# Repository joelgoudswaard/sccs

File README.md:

<h1>
  
  The Singularity Camper Control System
</h1>

The SCCS is a control system for the electrics in your caravan or camper trailer. It replaces a switch panel and battery/water gauges etc. with a modern touchscreen UI that provides:
- Automated control of lighting based on sunset/sunrise times and door/panel open and closes.
- Display of important information:
  - Battery level and usage
  - Solar generation
  - Water tank levels
  - Location data
  - outside/fridge temperature and weather forecasts
  - Sonos speakers

The system is made up of a Raspberry Pi and custom PCB, the SCCS Core that is the central hub where all field wiring connects to.

The SCCS software configures the Raspberry Pi as a router so that Internet can be distributed from a USB/Wi-Fi hotspot or Starlink through a downstream WAP, enabling a local Wi-Fi network that gives your devices access to the UI and provides ad-filtered Internet access.

Networking services — NAT, DNS, DHCP, and ad-filtering — are provided by nftables and Pi-hole and configured during installation. That same LAN step installs UniFi OS Server so UniFi access points can be adopted locally at `https://10.10.10.1:11443`. Apple HomeKit and Google Home can be configured to enable voice commands of lighting through Siri or Gemini. Cloudflare Tunnels is supported for remote access to the system while away from the caravan/camper.

An interactive demo is available at [demo.singularityautomation.com.au](https://demo.singularityautomation.com.au).

## Getting started

## Quickstart

1. Order SCCS Core PCB from JLCPCB by uploading the contents of the `/kicad/production` folder to JLCPCB. Get PCBA (assembly) done as well - you will receive a warning during the component placement stage that the same component is mapped to multiple parts. This is intentional, tick the checkboxes to include them in the build and continue.
2. Install wiring and SCCS core.
3. Install the software with the install command:

```bash
curl -fsSL https://raw.githubusercontent.com/joelgoudswaard/sccs/main/install.sh -o /tmp/sccs-install.sh && sudo bash /tmp/sccs-install.sh
```

Full instructions are in the [project wiki](https://github.com/joelgoudswaard/sccs/wiki/).

## System overview

A touchscreen in the kitchen or similar area shows the main user interface and is also reachable from phones or tablets on the LAN:

- Dimmable lighting sliders with red/white anti-bug mode and on/off buttons for non-dimmable loads (water, lighting, fridge circuits)
- Ambient lights that fade on as it gets dark
- One-touch lighting scenes
- Control of Sonos speakers
- Light/dark UI themes and an extensive settings page
- Integration with Apple HomeKit and Google Home

## Display of Environmental information

- Water tank level
- Current temperature and fridge/freezer temperatures
- Current battery charge, voltage, current consumption, estimated power remaining and current/daily solar generation
- GPS coordinates, closest suburb, altitude, satellite quality, sunrise/sunset, and the day/evening/night timing that drives automation
- 4 Day weather forecast, humidity and expected overnight temperature if Internet is present
- Internet connection quality details
- What lights are on and what doors or panels are open
- Health status of connected hardware modules like solar or GPS

## Hardware architecture

- Raspberry Pi 4/5
- Dual ESP32-S3s for 16 channels of PWM dimming via MOSFETs
- u-blox NEO-M9N GPS for location data
- Victron SmartShunt and SmartSolar support for battery and solar monitoring
- WS281X addressable LED strip outputs
- 10A relays for non-dimmable loads like lighting circuits, floodlights and water pumps
- Reed switch inputs for door/panel sensing and triggering of lights
- 1-Wire bus for temperature sensors
- Water tank level sensor input
- Spare channels for everything for expansion

## Hardware and User Interface

### SCCS Core

<table>
  <tr>
    <td align="center" width="50%"></td>
    <td align="center" width="50%"></td>
  </tr>
  <tr>
    <td align="center"><strong>Top (bare board)</strong></td>
    <td align="center"><strong>Top (with Raspberry Pi fitted)</strong></td>
  </tr>
  <tr>
    <td align="center"></td>
    <td align="center"></td>
  </tr>
  <tr>
    <td align="center"><strong>Bottom</strong></td>
    <td align="center"><strong>Isometric (with Raspberry Pi fitted)</strong></td>
  </tr>
</table>

### 3D Printable Mount

<table>
  <tr>
    <td align="center" width="50%"></td>
    <td align="center" width="50%"></td>
  </tr>
  <tr>
    <td align="center"><strong>3D printable frame (top)</strong></td>
    <td align="center"><strong>3D printable frame (isometric)</strong></td>
  </tr>
</table>

### User Interface

<table>
  <tr>
    <td align="center" width="50%"></td>
    <td align="center" width="50%"></td>
  </tr>
  <tr>
    <td align="center"><strong>Neumorphism (Dark) — iPad</strong></td>
    <td align="center"><strong>Neumorphism (Light) — iPad</strong></td>
  </tr>
  <tr>
    <td align="center"></td>
    <td align="center"></td>
  </tr>
  <tr>
    <td align="center"><strong>Glassmorphism (Dark) — iPad</strong></td>
    <td align="center"><strong>Glassmorphism (Dark) — iPad Lighting</strong></td>
  </tr>
  <tr>
    <td align="center"></td>
    <td align="center"></td>
  </tr>
  <tr>
    <td align="center"><strong>Neumorphism (Dark) — iPhone Portrait</strong></td>
    <td align="center"><strong>Neumorphism (Dark) — iPhone Landscape</strong></td>
  </tr>
</table>

---

## Documentation

Wiring, installation, configuration, and optional packages are on the **[project wiki](https://github.com/joelgoudswaard/sccs/wiki)** (start at [Home](https://github.com/joelgoudswaard/sccs/wiki/Home) for the setup path and glossary).

| Topic | Wiki page |
|-------|-----------|
| Overview, setup path, glossary | [Home](https://github.com/joelgoudswaard/sccs/wiki/Home) |
| Shopping list and wiring | [Wiring and Hardware](https://github.com/joelgoudswaard/sccs/wiki/Wiring-and-Hardware) |
| Imaging the Pi and installer | [Software Installation](https://github.com/joelgoudswaard/sccs/wiki/Software-Installation) |
| `sccs.conf`, phases, lights, sensors | [Software Configuration](https://github.com/joelgoudswaard/sccs/wiki/Software-Configuration) |
| SmartShunt / SmartSolar Bluetooth | [Victron Setup](https://github.com/joelgoudswaard/sccs/wiki/Victron-Setup) |
| Apple Home app / Siri (optional) | [HomeKit](https://github.com/joelgoudswaard/sccs/wiki/HomeKit) |
| Google Home / Gemini (optional) | [Google Home](https://github.com/joelgoudswaard/sccs/wiki/Google-Home) |
| LAN, NAT, Pi-hole, USB internet | [Networking](https://github.com/joelgoudswaard/sccs/wiki/Networking) |
| UniFi controller (optional) | [UniFi OS Server](https://github.com/joelgoudswaard/sccs/wiki/UniFi-OS-Server) |

---

## License

Licensed under the [MIT License](LICENSE).

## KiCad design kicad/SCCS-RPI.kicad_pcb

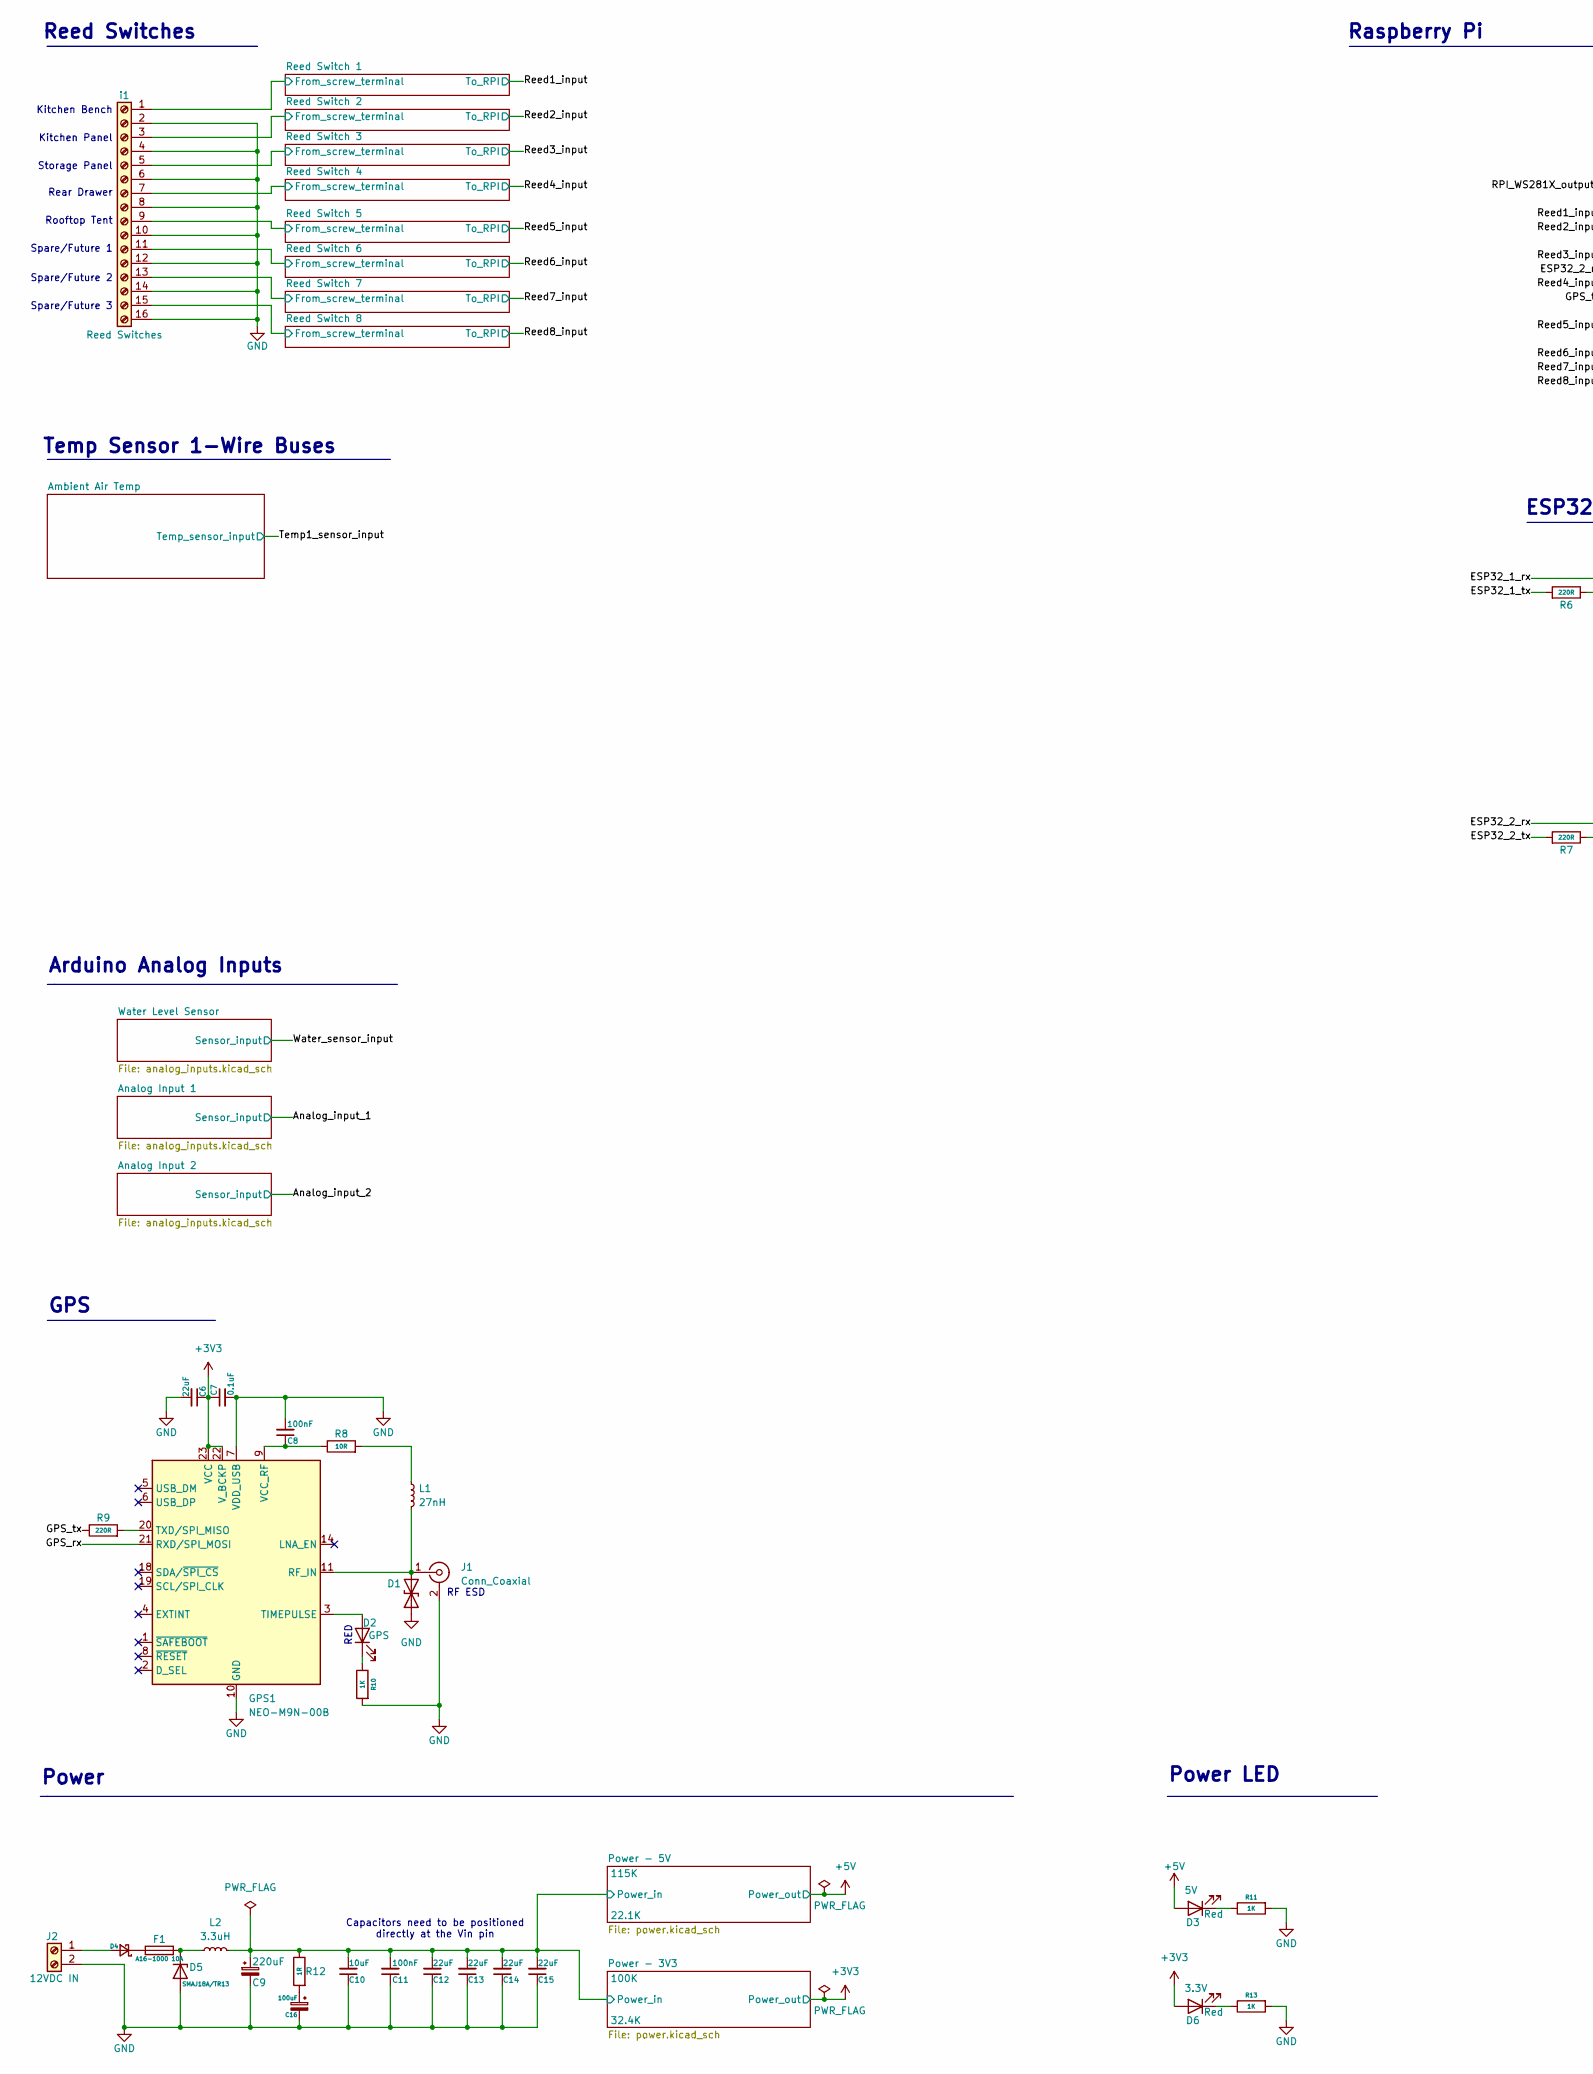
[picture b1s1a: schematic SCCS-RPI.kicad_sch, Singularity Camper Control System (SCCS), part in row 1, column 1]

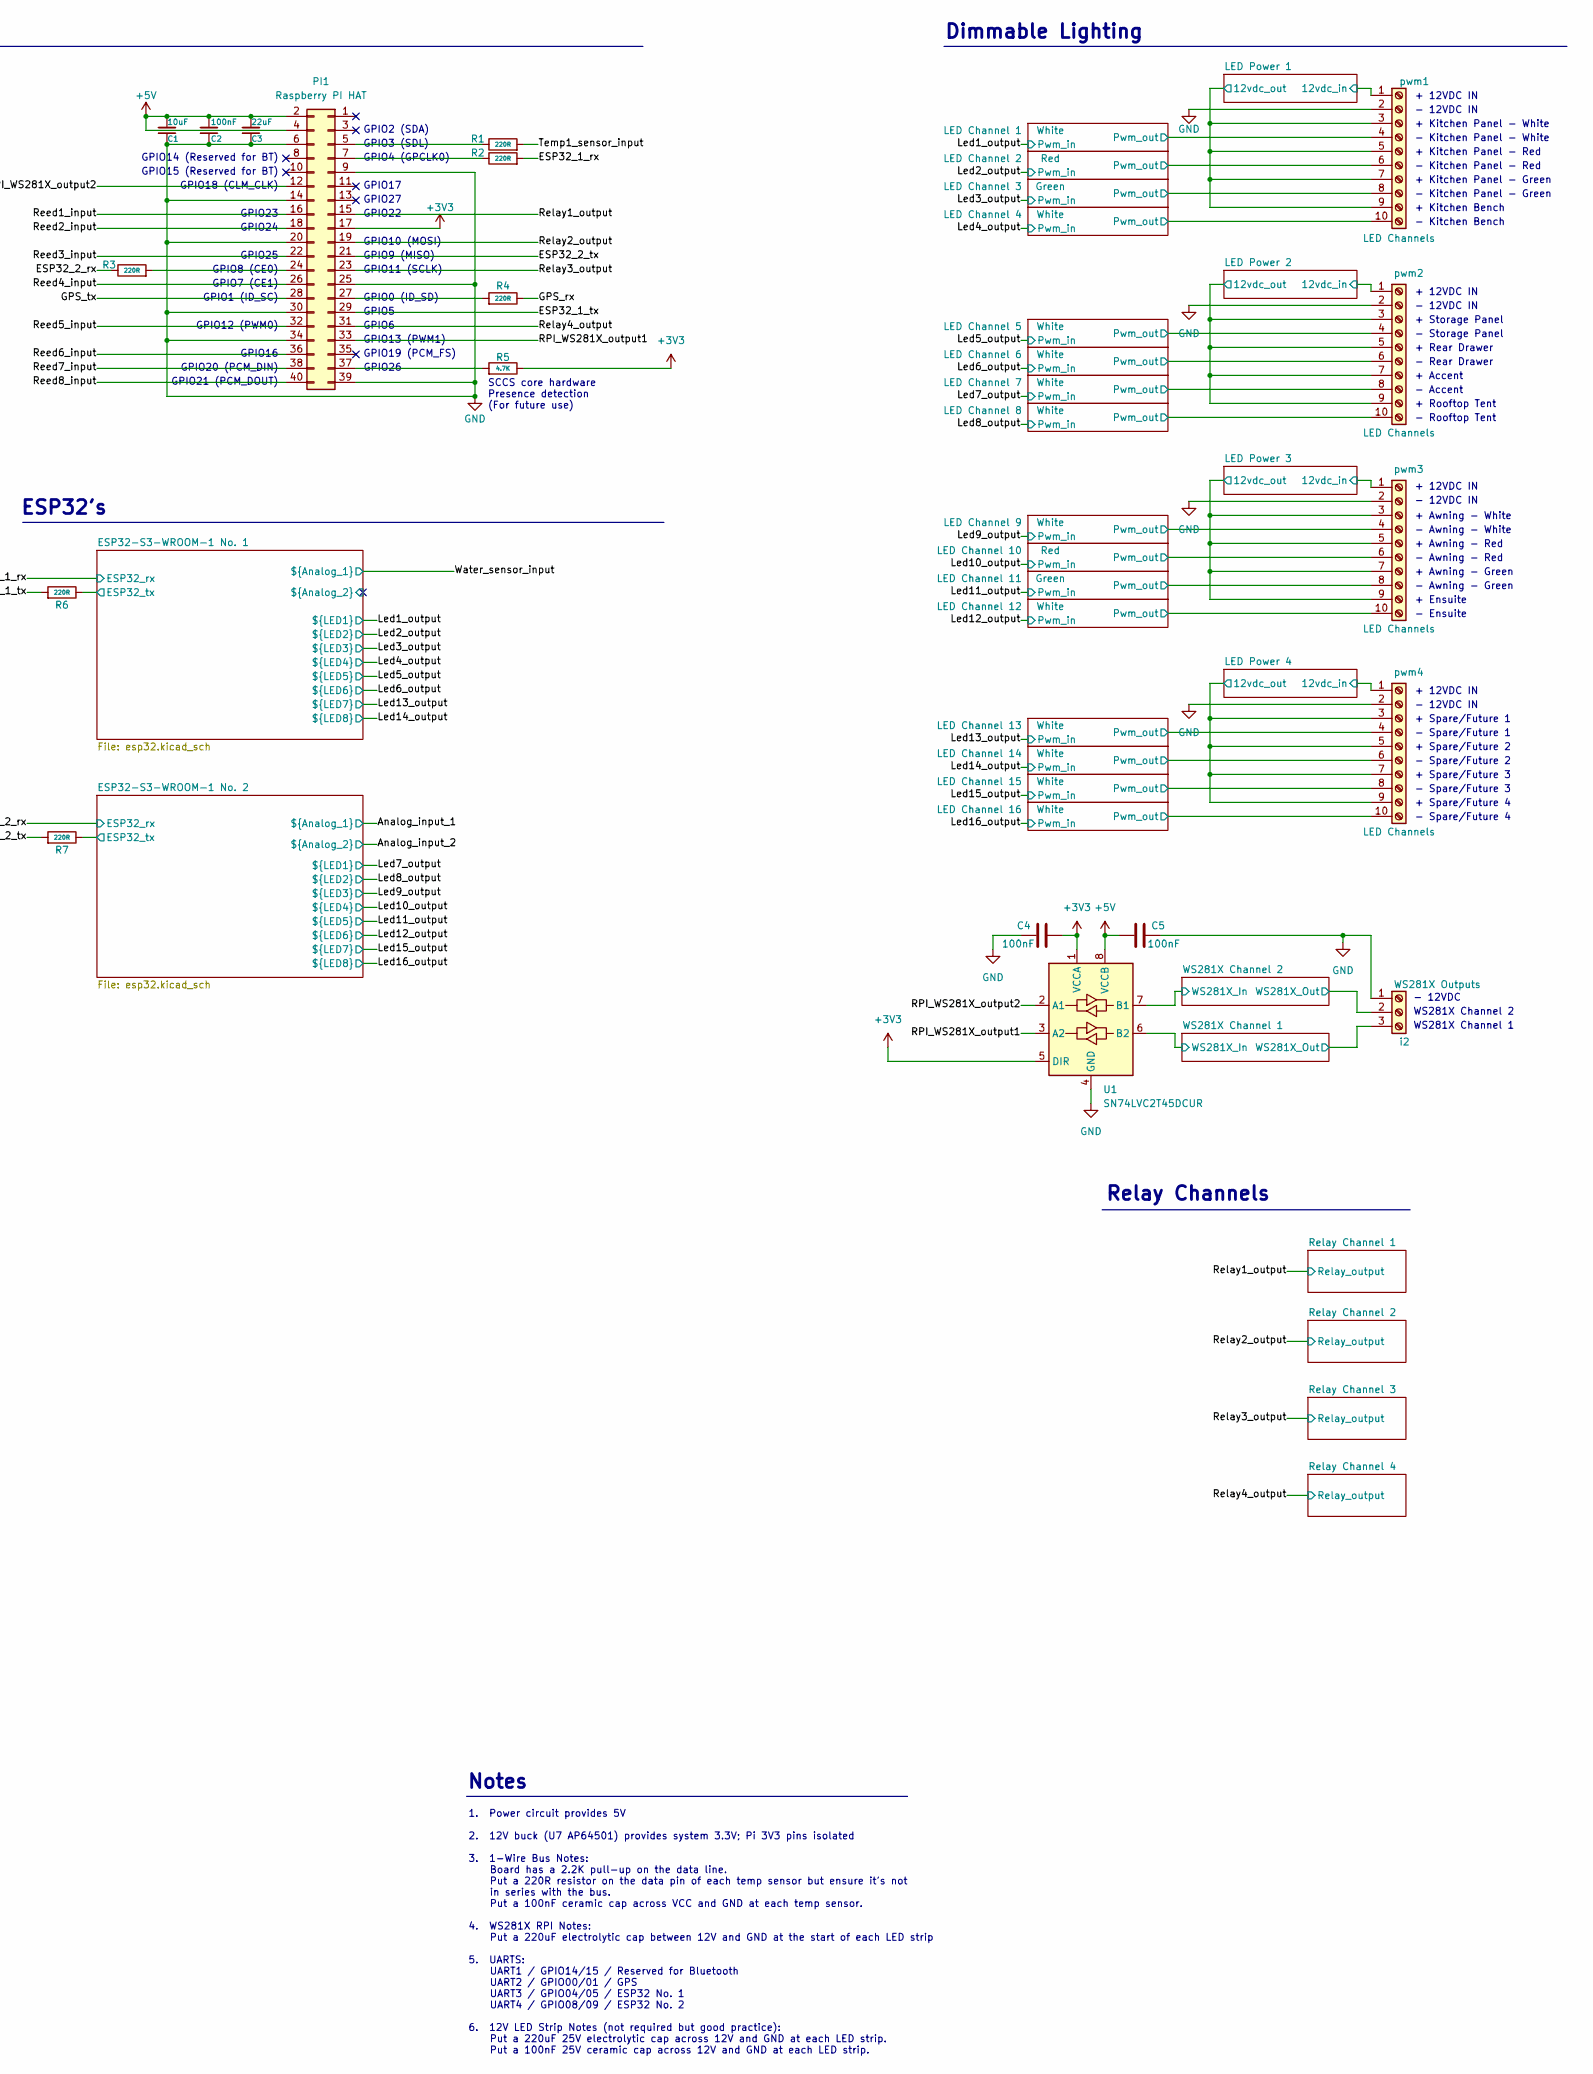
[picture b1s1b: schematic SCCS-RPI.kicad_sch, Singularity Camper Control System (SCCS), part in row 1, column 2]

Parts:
C1, C10: 10uF; C_0805_2012Metric; LCSC Part # C15850
C2, C8, C11: 100nF; C_0805_2012Metric; LCSC Part # C49678
C3, C6, C12, C13, C14, C15: 22uF; C_0805_2012Metric; LCSC Part # C86816
C4, C5: 100nF; C_0603_1608Metric; LCSC Part # C1590
C7: 0.1uF; C_0805_2012Metric; LCSC Part # C86041
C9: 220uF; CP_Elec_8x10; LCSC Part # C165536
C16: 100uF; CP_Radial_D6.3mm_P2.50mm; LCSC Part # C44587
D1: ESD103-B1-02EL; D_0402_1005Metric; LCSC Part # C535146
D2: GPS; LED_0603_1608Metric; LCSC Part # C2286
D3: 5V; LED_0603_1608Metric; LCSC Part # C2286
D4: D_PowerDI-5; LCSC Part # C2759901
D5: SMAJ18A/TR13; D_SMB; LCSC Part # C571369
D6: 3.3V; LED_0603_1608Metric; LCSC Part # C2286
F1: A16-1000 10A; Fuse_Bourns_MF-RG1000; LCSC Part # C135398
GPS1: NEO-M9N-00B; ublox_NEO; LCSC Part # C5119087
J1: Conn_Coaxial; SMA_Amphenol_132134-11_Vertical; LCSC Part # C20415804
J2: 12VDC IN; TerminalBlock_Phoenix_MKDS-1,5-2-5.08_1x02_P5.08mm_Horizont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; LCSC Part # C8445
L1: 27nH; L_0603_1608Metric; LCSC Part # C162550
L2: 3.3uH; L_SXN_SMDRI127; LCSC Part # C24550
PI1: Raspberry PI HAT; PinSocket_2x20_P2.54mm_Vertical; LCSC Part # C132132
R1, R2, R3, R4, R6, R7, R9: 220R; R_0805_2012Metric; LCSC Part # C17557
R5: 4.7K; R_0805_2012Metric; LCSC Part # C17673
R8: 10R; R_0805_2012Metric; LCSC Part # C17415
R10, R11, R13: 1K; R_0402_1005Metric; LCSC Part # C11702
R12: 1R; R_0805_2012Metric; LCSC Part # C25271
U1: SN74LVC2T45DCUR; VSSOP-8_2.3x2mm_P0.5mm; LCSC Part # C15741
i1: Reed Switches; TerminalBlock_Phoenix_MKDS-1,5-16-5.08_1x16_P5.08mm_Horizon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; LCSC Part # C508906
i2: WS281X Outputs; TerminalBlock_Phoenix_MKDS-1,5-3-5.08_1x03_P5.08mm_Horizont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; LCSC Part # C8412
pwm1, pwm2, pwm3, pwm4: LED Channels; TerminalBlock_Phoenix_MKDS-1,5-10-5.08_1x10_P5.08mm_Horizon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; LCSC Part # C29173

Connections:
+3V3: C4.2, C6.1, C7.1, D6.2 (A), GPS1.22 (V_BCKP), GPS1.23 (VCC), PI1.17, R5.1, U1.1 (VCCA), U1.5 (DIR); also elsewhere on the board
+5V: C1.2, C2.2, C3.2, C5.2, D3.2 (A), PI1.2, PI1.4, U1.8 (VCCB); also elsewhere on the board
/ESP32-S3-WROOM-1 No. 1/ESP32_tx: R6.1; also elsewhere on the board
/ESP32-S3-WROOM-1 No. 2/ESP32_tx: R7.1; also elsewhere on the board
/ESP32_1_rx: R2.2; also elsewhere on the board
/ESP32_1_tx: PI1.29, R6.2
/ESP32_2_rx: R3.1; also elsewhere on the board
/ESP32_2_tx: PI1.21, R7.2
/GPS_rx: GPS1.21 (RXD/SPI_MOSI), R4.1
/GPS_tx: PI1.28, R9.1
/LED Channel 1/Pwm_out: pwm1.4; also elsewhere on the board
/LED Channel 2/Pwm_out: pwm1.6; also elsewhere on the board
/LED Channel 3/Pwm_out: pwm1.8; also elsewhere on the board
/LED Channel 4/Pwm_out: pwm1.10; also elsewhere on the board
/LED Channel 5/Pwm_out: pwm2.4; also elsewhere on the board
/LED Channel 6/Pwm_out: pwm2.6; also elsewhere on the board
/LED Channel 7/Pwm_out: pwm2.8; also elsewhere on the board
/LED Channel 8/Pwm_out: pwm2.10; also elsewhere on the board
/LED Channel 9/Pwm_out: pwm3.4; also elsewhere on the board
/LED Channel 10/Pwm_out: pwm3.6; also elsewhere on the board
/LED Channel 11/Pwm_out: pwm3.8; also elsewhere on the board
/LED Channel 12/Pwm_out: pwm3.10; also elsewhere on the board
/LED Channel 13/Pwm_out: pwm4.4; also elsewhere on the board
/LED Channel 14/Pwm_out: pwm4.6; also elsewhere on the board
/LED Channel 15/Pwm_out: pwm4.8; also elsewhere on the board
/LED Channel 16/Pwm_out: pwm4.10; also elsewhere on the board
/LED Power 1/12vdc_in: pwm1.1; also elsewhere on the board
/LED Power 1/12vdc_out: pwm1.3, pwm1.5, pwm1.7, pwm1.9; also elsewhere on the board
/LED Power 2/12vdc_in: pwm2.1; also elsewhere on the board
/LED Power 2/12vdc_out: pwm2.3, pwm2.5, pwm2.7, pwm2.9; also elsewhere on the board
/LED Power 3/12vdc_in: pwm3.1; also elsewhere on the board
/LED Power 3/12vdc_out: pwm3.3, pwm3.5, pwm3.7, pwm3.9; also elsewhere on the board
/LED Power 4/12vdc_in: pwm4.1; also elsewhere on the board
/LED Power 4/12vdc_out: pwm4.3, pwm4.5, pwm4.7, pwm4.9; also elsewhere on the board
/Power - 3V3/Power_in: C9.1, C10.2, C11.2, C12.2, C13.2, C14.2, C15.2, L2.2, R12.1; also elsewhere on the board
/RPI_WS281X_output1: PI1.33, U1.3 (A2)
/RPI_WS281X_output2: PI1.12, U1.2 (A1)
/Reed1_input: PI1.16; also elsewhere on the board
/Reed2_input: PI1.18; also elsewhere on the board
/Reed3_input: PI1.22; also elsewhere on the board
/Reed4_input: PI1.26; also elsewhere on the board
/Reed5_input: PI1.32; also elsewhere on the board
/Reed6_input: PI1.36; also elsewhere on the board
/Reed7_input: PI1.38; also elsewhere on the board
/Reed8_input: PI1.40; also elsewhere on the board
/Reed Switch 1/From_screw_terminal: i1.1; also elsewhere on the board
/Reed Switch 2/From_screw_terminal: i1.3; also elsewhere on the board
/Reed Switch 3/From_screw_terminal: i1.5; also elsewhere on the board
/Reed Switch 4/From_screw_terminal: i1.7; also elsewhere on the board
/Reed Switch 5/From_screw_terminal: i1.9; also elsewhere on the board
/Reed Switch 6/From_screw_terminal: i1.11; also elsewhere on the board
/Reed Switch 7/From_screw_terminal: i1.13; also elsewhere on the board
/Reed Switch 8/From_screw_terminal: i1.15; also elsewhere on the board
/Relay1_output: PI1.15; also elsewhere on the board
/Relay2_output: PI1.19; also elsewhere on the board
/Relay3_output: PI1.23; also elsewhere on the board
/Relay4_output: PI1.31; also elsewhere on the board
/Temp1_sensor_input: R1.2; also elsewhere on the board
/WS281X Channel 1/WS281X_In: U1.6 (B2); also elsewhere on the board
/WS281X Channel 1/WS281X_Out: i2.3; also elsewhere on the board
/WS281X Channel 2/WS281X_In: U1.7 (B1); also elsewhere on the board
/WS281X Channel 2/WS281X_Out: i2.2; also elsewhere on the board
GND: C1.1, C2.1, C3.1, C4.1, C5.1, C6.2, C7.2, C8.2, C9.2, C10.1, C11.1, C12.1, C13.1, C14.1, C15.1, C16.2, D1.1 (A1), D5.2 (A), GPS1.7 (VDD_USB), GPS1.10 (GND), GPS1.12 (GND), GPS1.13 (GND), GPS1.24 (GND), J1.2 (Ext), J2.2, PI1.6, PI1.9, PI1.14, PI1.20, PI1.25, PI1.30, PI1.34, PI1.39, R10.2, R11.2, R13.2, U1.4 (GND), i1.2, i1.4, i1.6, i1.8, i1.10, i1.12, i1.14, i1.16, i2.1, pwm1.2, pwm2.2, pwm3.2, pwm4.2; also elsewhere on the board
unnamed: C16.1, R12.2
unnamed: D1.2 (A2), GPS1.11 (RF_IN), J1.1 (In), L1.2
unnamed: D2.2 (A), GPS1.3 (TIMEPULSE)
unnamed: D2.1 (K), R10.1
unnamed: D3.1 (K), R11.1
unnamed: D4.2 (A), J2.1
unnamed: D4.1 (K), F1.1
unnamed: D5.1 (K), F1.2, L2.1
unnamed: D6.1 (K), R13.1
unnamed: GPS1.20 (TXD/SPI_MISO), R9.2
unnamed: C8.1, GPS1.9 (VCC_RF), R8.1
unnamed: L1.1, R8.2
unnamed: PI1.5, R1.1
unnamed: PI1.7, R2.1
unnamed: PI1.24, R3.2
unnamed: PI1.27, R4.2
unnamed: PI1.37, R5.2

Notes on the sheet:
+ Awning - White
- Spare/Future 3
GPIO1 (ID_SC)
Capacitors need to be positioned directly at the Vin pin
+ Spare/Future 1
WS281X Channel 1
GPIO12 (PWM0)
Rooftop Tent
Temp Sensor 1-Wire Buses
GPIO15 (Reserved for BT)
- 12VDC IN
SCCS core hardware Presence detection (For future use)
GPIO22
GPIO23
- Kitchen Panel - Red
Spare/Future 3
GPIO20 (PCM_DIN)
1. Power circuit provides 5V 2. 12V buck (U7 AP64501) provides system 3.3V; Pi 3V3 pins isolated 3. 1-Wire Bus Notes: Board has a 2.2K pull-up on the data line. Put a 220R resistor on the data pin of each temp sensor but ensure it's not in series with the bus. Put a 100nF ceramic cap across VCC and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
- Rear Drawer
ESP32's
+ Kitchen Bench
- Accent
RF ESD
GPIO25
GPIO27
+ 12VDC IN
GPIO11 (SCLK)
+ Storage Panel
+ Ensuite
- Kitchen Bench
GPIO7 (CE1)
Kitchen Bench
Notes
- Spare/Future 1
GPS
GPIO4 (GPCLK0)
- Rooftop Tent
Spare/Future 2
GPIO3 (SDL)
+ Awning - Green

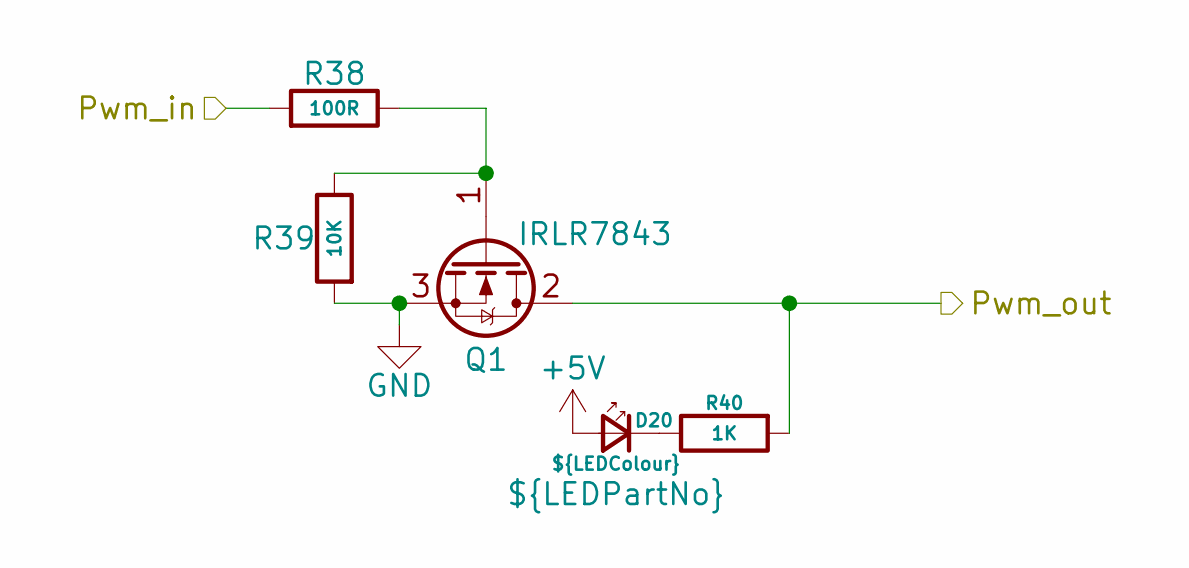
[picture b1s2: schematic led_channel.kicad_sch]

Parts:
D20: ${LEDColour}; LED_0603_1608Metric; LCSC Part # ${LEDPartNo}
Q1: IRLR7843; TO-252-2; LCSC Part # C21988
R38: 100R; R_0805_2012Metric; LCSC Part # C17408
R39: 10K; R_0805_2012Metric; LCSC Part # C17414
R40: 1K; R_0805_2012Metric; LCSC Part # C17513

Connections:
+5V: D20.2 (A); also elsewhere on the board
/LED Channel 1/Pwm_out: Q1.2 (D), R40.2; also elsewhere on the board
/Led1_output: R38.2; also elsewhere on the board
GND: Q1.3 (S), R39.2; also elsewhere on the board
unnamed: D20.1 (K), R40.1
unnamed: Q1.1 (G), R38.1, R39.1

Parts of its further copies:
Q2, Q3, Q4, Q5, Q6, Q7, Q8, Q9, Q10, Q11, Q12, Q13, Q14, Q15, Q16: IRLR7843; TO-252-2; LCSC Part # C21988
R41, R44, R47, R50, R53, R56, R59, R62, R65, R68, R71, R74, R77, R80, R83: 100R; R_0805_2012Metric; LCSC Part # C17408
R42, R45, R48, R51, R54, R57, R60, R63, R66, R69, R72, R75, R78, R81, R84: 10K; R_0805_2012Metric; LCSC Part # C17414
R43, R46, R49, R52, R55, R58, R61, R64, R67, R70, R73, R76, R79, R82, R85: 1K; R_0805_2012Metric; LCSC Part # C17513

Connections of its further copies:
/LED Channel 2/Pwm_out: Q2.2 (D), R43.2; also elsewhere on the board
/LED Channel 3/Pwm_out: Q3.2 (D), R46.2; also elsewhere on the board
/LED Channel 4/Pwm_out: Q4.2 (D), R49.2; also elsewhere on the board
/LED Channel 5/Pwm_out: Q5.2 (D), R52.2; also elsewhere on the board
/LED Channel 6/Pwm_out: Q6.2 (D), R55.2; also elsewhere on the board
/LED Channel 7/Pwm_out: Q7.2 (D), R58.2; also elsewhere on the board
/LED Channel 8/Pwm_out: Q8.2 (D), R61.2; also elsewhere on the board
/LED Channel 9/Pwm_out: Q9.2 (D), R64.2; also elsewhere on the board
/LED Channel 10/Pwm_out: Q10.2 (D), R67.2; also elsewhere on the board
/LED Channel 11/Pwm_out: Q11.2 (D), R70.2; also elsewhere on the board
/LED Channel 12/Pwm_out: Q12.2 (D), R73.2; also elsewhere on the board
/LED Channel 13/Pwm_out: Q13.2 (D), R76.2; also elsewhere on the board
/LED Channel 14/Pwm_out: Q14.2 (D), R79.2; also elsewhere on the board
/LED Channel 15/Pwm_out: Q15.2 (D), R82.2; also elsewhere on the board
/LED Channel 16/Pwm_out: Q16.2 (D), R85.2; also elsewhere on the board
/Led2_output: R41.2; also elsewhere on the board
/Led3_output: R44.2; also elsewhere on the board
/Led4_output: R47.2; also elsewhere on the board
/Led5_output: R50.2; also elsewhere on the board
/Led6_output: R53.2; also elsewhere on the board
/Led7_output: R56.2; also elsewhere on the board
/Led8_output: R59.2; also elsewhere on the board
/Led9_output: R62.2; also elsewhere on the board
/Led10_output: R65.2; also elsewhere on the board
/Led11_output: R68.2; also elsewhere on the board
/Led12_output: R71.2; also elsewhere on the board
/Led13_output: R74.2; also elsewhere on the board
/Led14_output: R77.2; also elsewhere on the board
/Led15_output: R80.2; also elsewhere on the board
/Led16_output: R83.2; also elsewhere on the board
GND: Q2.3 (S), Q3.3 (S), Q4.3 (S), Q5.3 (S), Q6.3 (S), Q7.3 (S), Q8.3 (S), Q9.3 (S), Q10.3 (S), Q11.3 (S), Q12.3 (S), Q13.3 (S), Q14.3 (S), Q15.3 (S), Q16.3 (S), R42.2, R45.2, R48.2, R51.2, R54.2, R57.2, R60.2, R63.2, R66.2, R69.2, R72.2, R75.2, R78.2, R81.2, R84.2; also elsewhere on the board
unnamed 95: R43.1; also elsewhere on the board
unnamed 96: R46.1; also elsewhere on the board
unnamed 97: R49.1; also elsewhere on the board
unnamed 98: R52.1; also elsewhere on the board
unnamed 99: R55.1; also elsewhere on the board
unnamed 100: R58.1; also elsewhere on the board
unnamed 101: R61.1; also elsewhere on the board
unnamed 102: R64.1; also elsewhere on the board
unnamed 103: R67.1; also elsewhere on the board
unnamed 104: R70.1; also elsewhere on the board
unnamed 105: R73.1; also elsewhere on the board
unnamed 106: R76.1; also elsewhere on the board
unnamed 107: R79.1; also elsewhere on the board
unnamed 108: R82.1; also elsewhere on the board
unnamed 109: R85.1; also elsewhere on the board
unnamed: Q2.1 (G), R41.1, R42.1
unnamed: Q3.1 (G), R44.1, R45.1
unnamed: Q4.1 (G), R47.1, R48.1
unnamed: Q5.1 (G), R50.1, R51.1
unnamed: Q6.1 (G), R53.1, R54.1
unnamed: Q7.1 (G), R56.1, R57.1
unnamed: Q8.1 (G), R59.1, R60.1
unnamed: Q9.1 (G), R62.1, R63.1
unnamed: Q10.1 (G), R65.1, R66.1
unnamed: Q11.1 (G), R68.1, R69.1
unnamed: Q12.1 (G), R71.1, R72.1
unnamed: Q13.1 (G), R74.1, R75.1
unnamed: Q14.1 (G), R77.1, R78.1
unnamed: Q15.1 (G), R80.1, R81.1
unnamed: Q16.1 (G), R83.1, R84.1

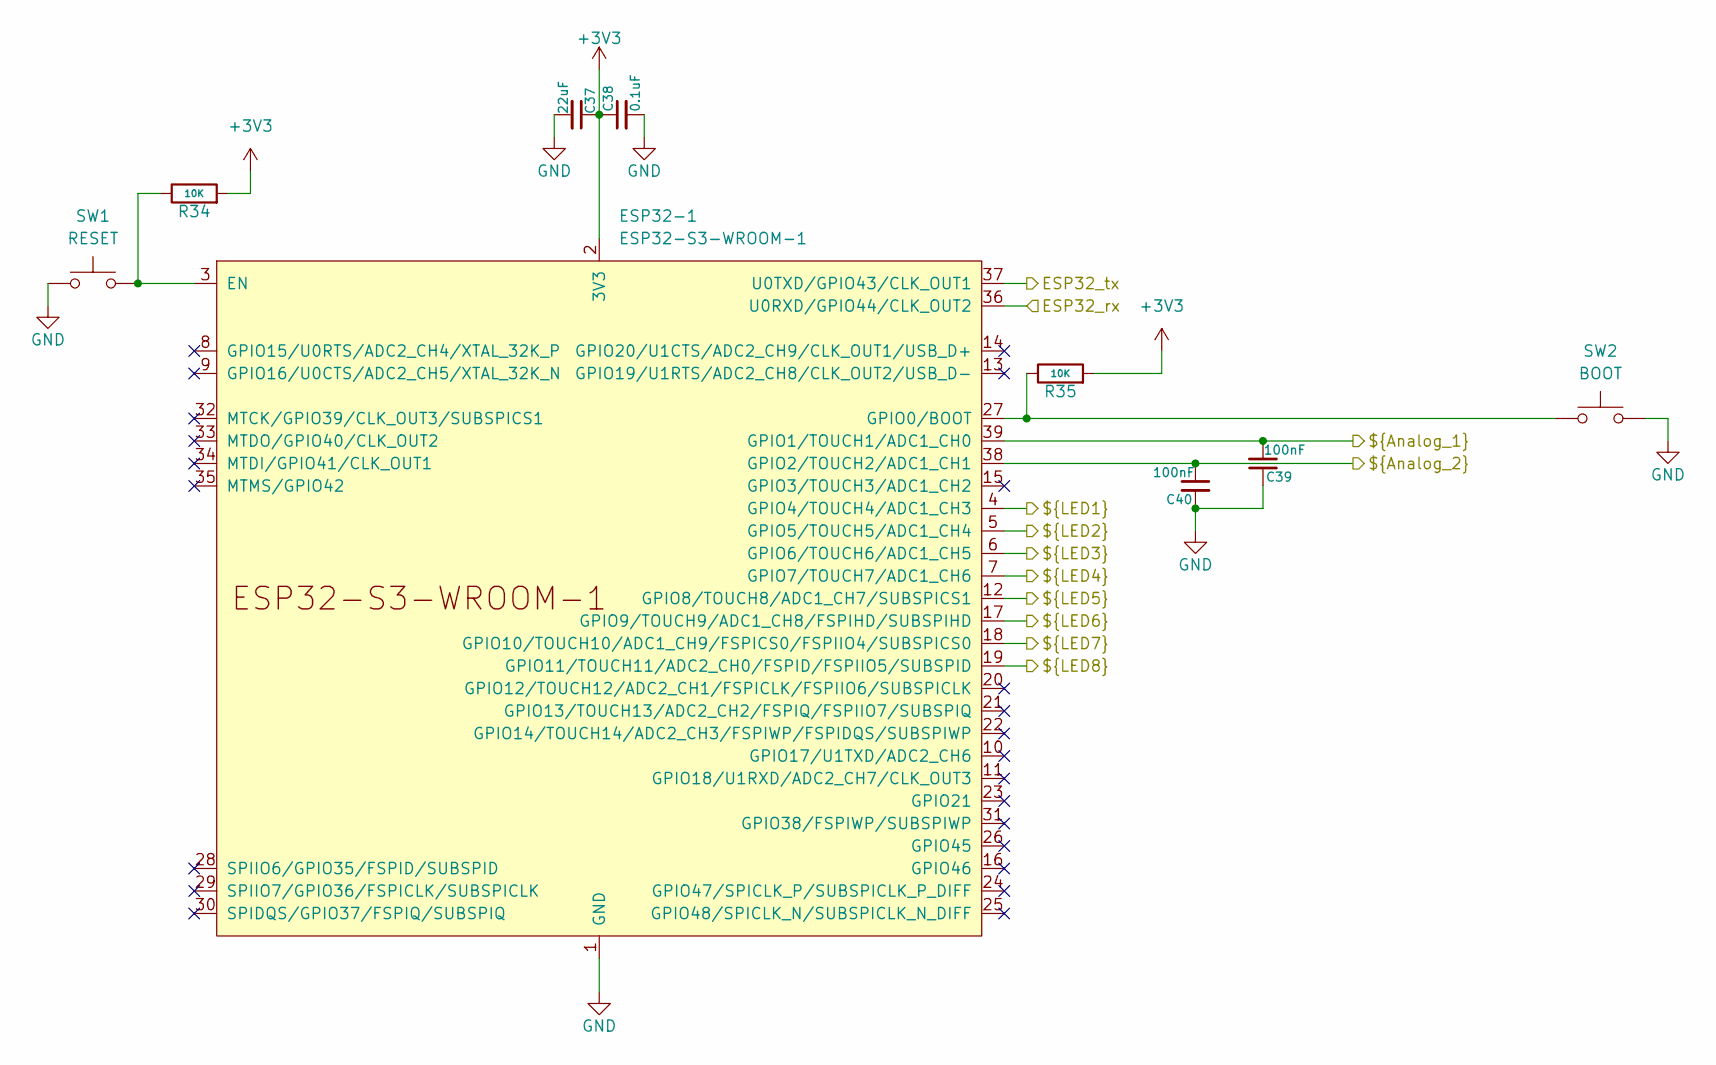
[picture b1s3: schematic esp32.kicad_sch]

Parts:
C37: 22uF; C_0805_2012Metric; LCSC Part # C86816
C38: 0.1uF; C_0805_2012Metric; LCSC Part # C86041
C39, C40: 100nF; C_0402_1005Metric; LCSC Part # C60474
ESP32-1: ESP32-S3-WROOM-1; ESP32-S3-WROOM-1U; LCSC Part # C3013946
R34, R35: 10K; R_0402_1005Metric; LCSC Part # C60490
SW1: RESET; SW_PUSH_1P1T_6x3.5mm_H5.0_APEM_MJTP1250; LCSC Part # C500070
SW2: BOOT; SW_PUSH_1P1T_6x3.5mm_H5.0_APEM_MJTP1250; LCSC Part # C500070

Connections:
+3V3: C37.1, C38.1, ESP32-1.2 (3V3), R34.2, R35.2; also elsewhere on the board
/ESP32-S3-WROOM-1 No. 1/ESP32_tx: ESP32-1.37 (U0TXD/GPIO43/CLK_OUT1); also elsewhere on the board
/ESP32-S3-WROOM-1 No. 1/NC: C40.1, ESP32-1.38 (GPIO2/TOUCH2/ADC1_CH1)
/ESP32_1_rx: ESP32-1.36 (U0RXD/GPIO44/CLK_OUT2); also elsewhere on the board
/Led1_output: ESP32-1.4 (GPIO4/TOUCH4/ADC1_CH3); also elsewhere on the board
/Led2_output: ESP32-1.5 (GPIO5/TOUCH5/ADC1_CH4); also elsewhere on the board
/Led3_output: ESP32-1.6 (GPIO6/TOUCH6/ADC1_CH5); also elsewhere on the board
/Led4_output: ESP32-1.7 (GPIO7/TOUCH7/ADC1_CH6); also elsewhere on the board
/Led5_output: ESP32-1.12 (GPIO8/TOUCH8/ADC1_CH7/SUBSPICS1); also elsewhere on the board
/Led6_output: ESP32-1.17 (GPIO9/TOUCH9/ADC1_CH8/FSPIHD/SUBSPIHD); also elsewhere on the board
/Led13_output: ESP32-1.18 (GPIO10/TOUCH10/ADC1_CH9/FSPICS0/FSPIIO4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); also elsewhere on the board
/Led14_output: ESP32-1.19 (GPIO11/TOUCH11/ADC2_CH0/FSPID/FSPIIO5/S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); also elsewhere on the board
/Water_sensor_input: C39.2, ESP32-1.39 (GPIO1/TOUCH1/ADC1_CH0); also elsewhere on the board
GND: C37.2, C38.2, C39.1, C40.2, ESP32-1.1 (GND), ESP32-1.40 (GND), ESP32-1.41 (GND), SW1.1, SW2.1; also elsewhere on the board
unnamed: ESP32-1.3 (EN), R34.1, SW1.2
unnamed: ESP32-1.27 (GPIO0/BOOT), R35.1, SW2.2

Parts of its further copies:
C41: 22uF; C_0805_2012Metric; LCSC Part # C86816
C42: 0.1uF; C_0805_2012Metric; LCSC Part # C86041
C43, C44: 100nF; C_0402_1005Metric; LCSC Part # C60474
ESP32-2: ESP32-S3-WROOM-1; ESP32-S3-WROOM-1U; LCSC Part # C3013946
R36, R37: 10K; R_0402_1005Metric; LCSC Part # C60490
SW3: RESET; SW_PUSH_1P1T_6x3.5mm_H5.0_APEM_MJTP1250; LCSC Part # C500070
SW4: BOOT; SW_PUSH_1P1T_6x3.5mm_H5.0_APEM_MJTP1250; LCSC Part # C500070

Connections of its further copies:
+3V3: C41.1, C42.1, ESP32-2.2 (3V3), R36.2, R37.2; also elsewhere on the board
/Analog_input_1: C43.2, ESP32-2.39 (GPIO1/TOUCH1/ADC1_CH0); also elsewhere on the board
/Analog_input_2: C44.1, ESP32-2.38 (GPIO2/TOUCH2/ADC1_CH1); also elsewhere on the board
/ESP32-S3-WROOM-1 No. 2/ESP32_tx: ESP32-2.37 (U0TXD/GPIO43/CLK_OUT1); also elsewhere on the board
/ESP32_2_rx: ESP32-2.36 (U0RXD/GPIO44/CLK_OUT2); also elsewhere on the board
/Led7_output: ESP32-2.4 (GPIO4/TOUCH4/ADC1_CH3); also elsewhere on the board
/Led8_output: ESP32-2.5 (GPIO5/TOUCH5/ADC1_CH4); also elsewhere on the board
/Led9_output: ESP32-2.6 (GPIO6/TOUCH6/ADC1_CH5); also elsewhere on the board
/Led10_output: ESP32-2.7 (GPIO7/TOUCH7/ADC1_CH6); also elsewhere on the board
/Led11_output: ESP32-2.12 (GPIO8/TOUCH8/ADC1_CH7/SUBSPICS1); also elsewhere on the board
/Led12_output: ESP32-2.17 (GPIO9/TOUCH9/ADC1_CH8/FSPIHD/SUBSPIHD); also elsewhere on the board
/Led15_output: ESP32-2.18 (GPIO10/TOUCH10/ADC1_CH9/FSPICS0/FSPIIO4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); also elsewhere on the board
/Led16_output: ESP32-2.19 (GPIO11/TOUCH11/ADC2_CH0/FSPID/FSPIIO5/S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); also elsewhere on the board
GND: C41.2, C42.2, C43.1, C44.2, ESP32-2.1 (GND), ESP32-2.40 (GND), ESP32-2.41 (GND), SW3.1, SW4.1; also elsewhere on the board
unnamed: ESP32-2.3 (EN), R36.1, SW3.2
unnamed: ESP32-2.27 (GPIO0/BOOT), R37.1, SW4.2

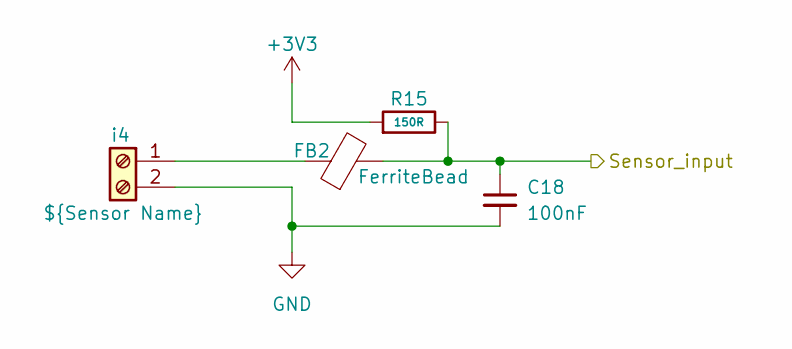
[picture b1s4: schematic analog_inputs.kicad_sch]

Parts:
C18: 100nF; C_0603_1608Metric; LCSC Part # C1590
FB2: FerriteBead; L_0603_1608Metric; LCSC Part # C1002
R15: 150R; R_0805_2012Metric; LCSC Part # C17471
i4: ${Sensor Name}; TerminalBlock_Phoenix_MKDS-1,5-2-5.08_1x02_P5.08mm_Horizont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; LCSC Part # C8445

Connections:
+3V3: R15.2; also elsewhere on the board
/Water_sensor_input: C18.1, FB2.2, R15.1; also elsewhere on the board
GND: C18.2, i4.2; also elsewhere on the board
unnamed: FB2.1, i4.1

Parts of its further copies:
C19, C20: 100nF; C_0603_1608Metric; LCSC Part # C1590
FB3, FB4: FerriteBead; L_0603_1608Metric; LCSC Part # C1002
R16, R17: 150R; R_0805_2012Metric; LCSC Part # C17471

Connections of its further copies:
+3V3: R16.2, R17.2; also elsewhere on the board
/Analog_input_1: C19.1, FB3.2, R16.1; also elsewhere on the board
/Analog_input_2: C20.1, FB4.2, R17.1; also elsewhere on the board
GND: C19.2, C20.2; also elsewhere on the board
unnamed 182: FB3.1; also elsewhere on the board
unnamed 183: FB4.1; also elsewhere on the board

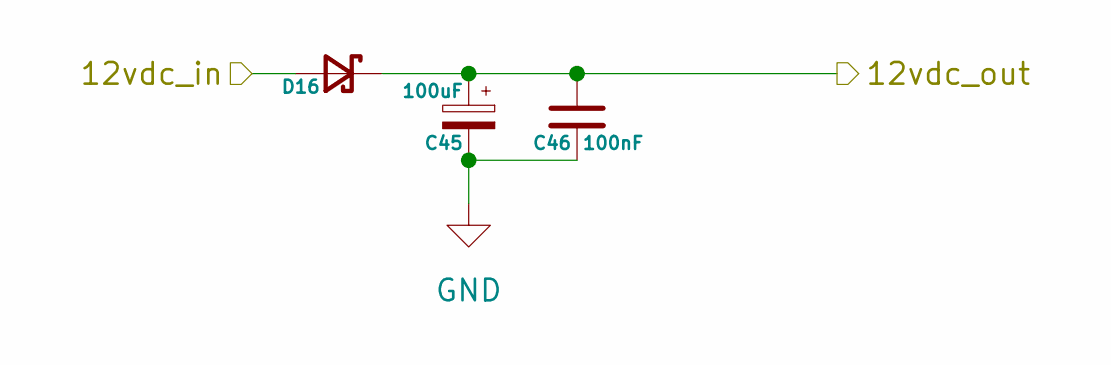
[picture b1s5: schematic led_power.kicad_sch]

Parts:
C45: 100uF; CP_Radial_D6.3mm_P2.50mm; LCSC Part # C44587
C46: 100nF; C_0805_2012Metric; LCSC Part # C49678
D16: D_PowerDI-5; LCSC Part # C2759901

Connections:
/LED Power 1/12vdc_in: D16.2 (A); also elsewhere on the board
/LED Power 1/12vdc_out: C45.1, C46.1, D16.1 (K); also elsewhere on the board
GND: C45.2, C46.2; also elsewhere on the board

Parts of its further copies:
C47, C49, C51: 100uF; CP_Radial_D6.3mm_P2.50mm; LCSC Part # C44587
C48, C50, C52: 100nF; C_0805_2012Metric; LCSC Part # C49678

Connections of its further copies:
/LED Power 2/12vdc_out: C47.1, C48.1; also elsewhere on the board
/LED Power 3/12vdc_out: C49.1, C50.1; also elsewhere on the board
/LED Power 4/12vdc_out: C51.1, C52.1; also elsewhere on the board
GND: C47.2, C48.2, C49.2, C50.2, C51.2, C52.2; also elsewhere on the board

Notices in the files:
kicad/SCCS-RPI.kicad_pcb:
© 2026 Joel Goudswaard
